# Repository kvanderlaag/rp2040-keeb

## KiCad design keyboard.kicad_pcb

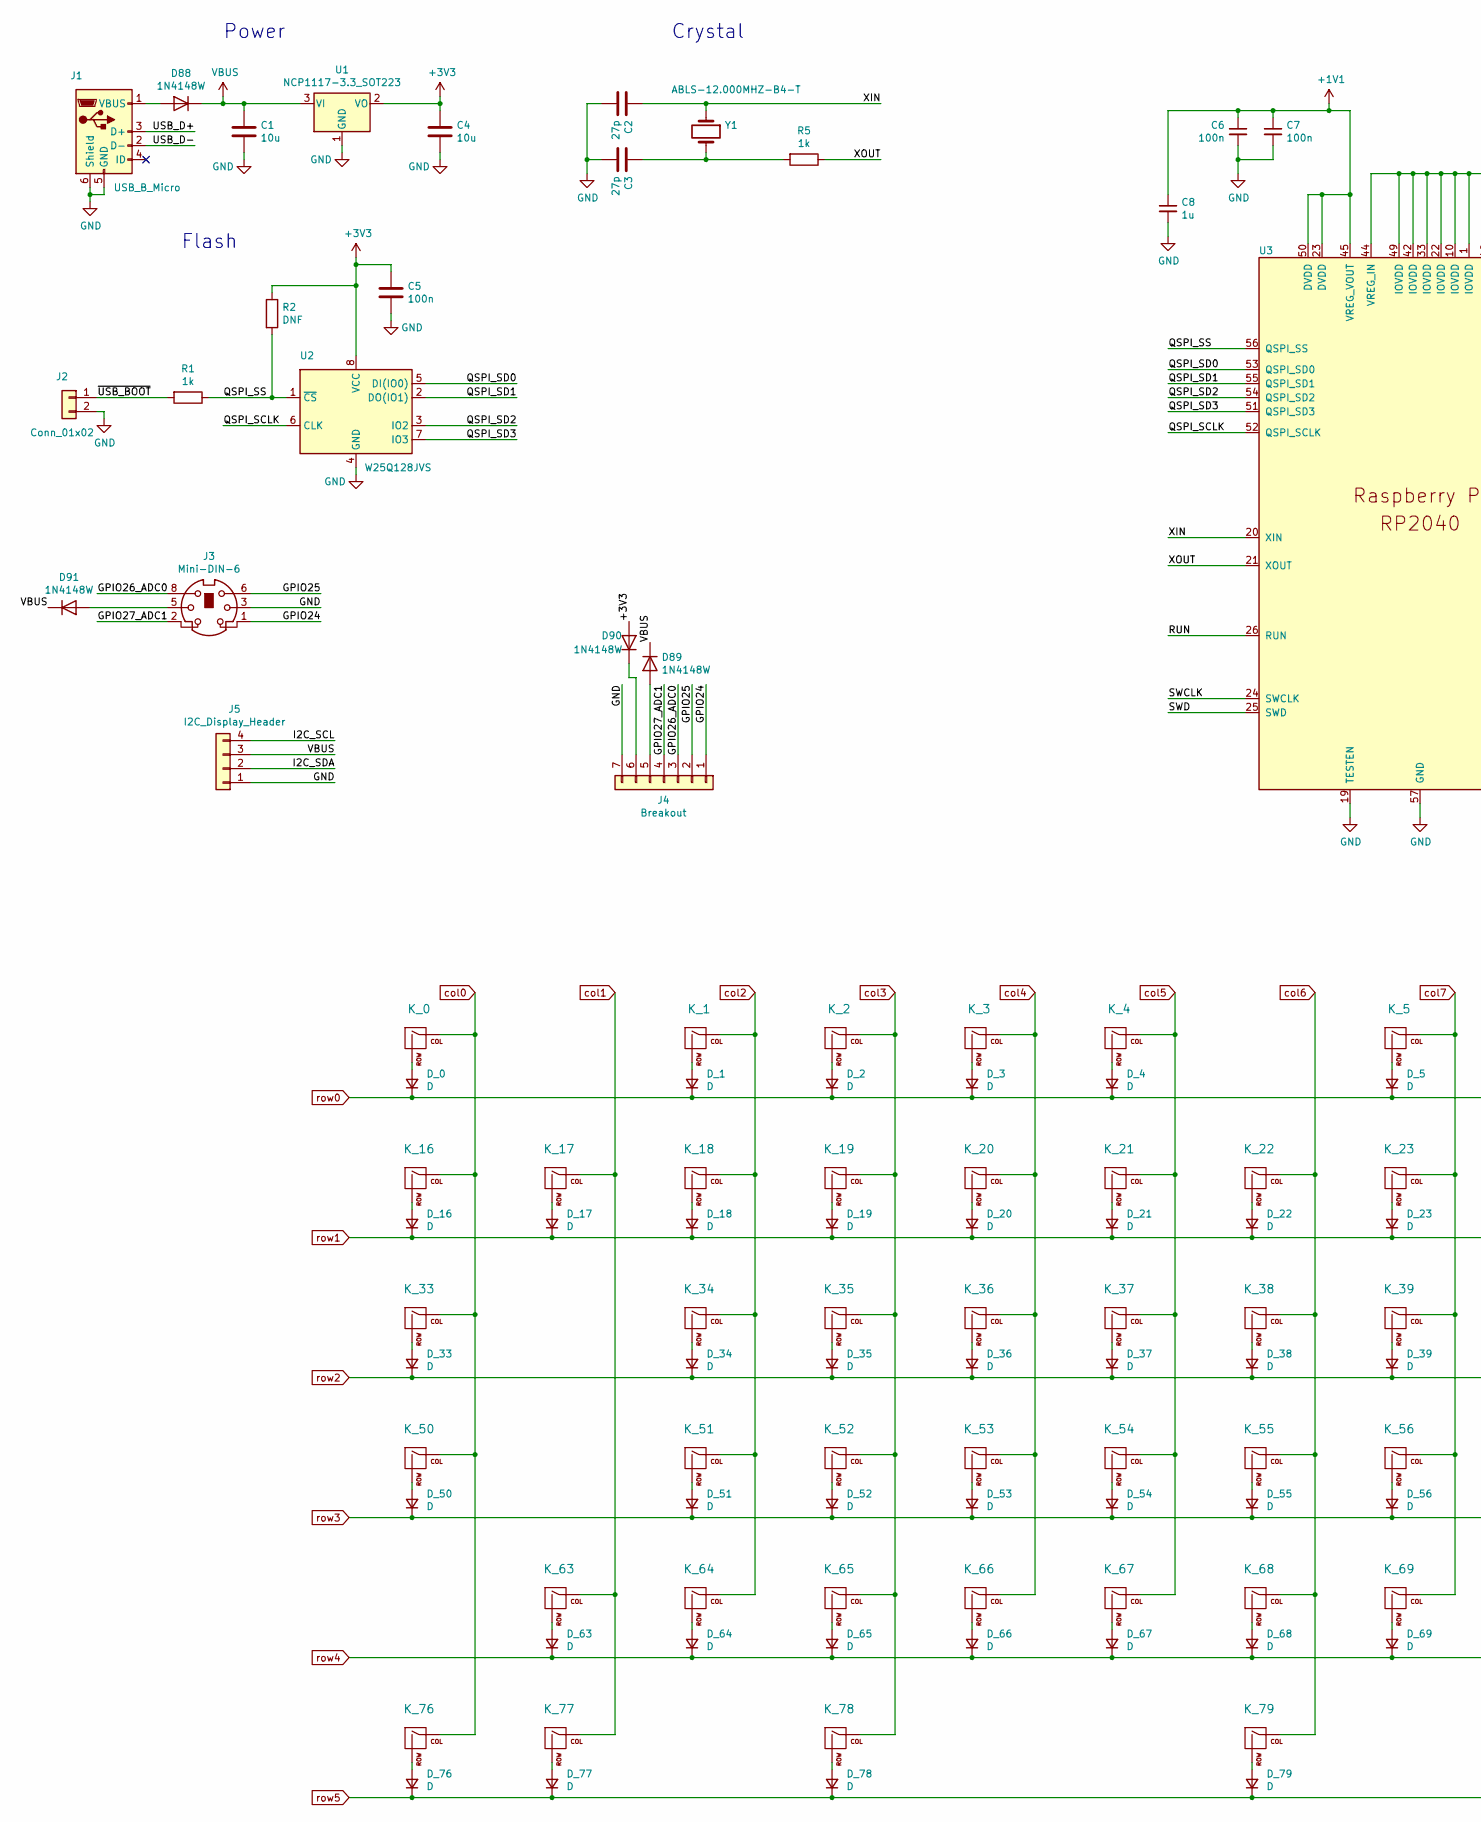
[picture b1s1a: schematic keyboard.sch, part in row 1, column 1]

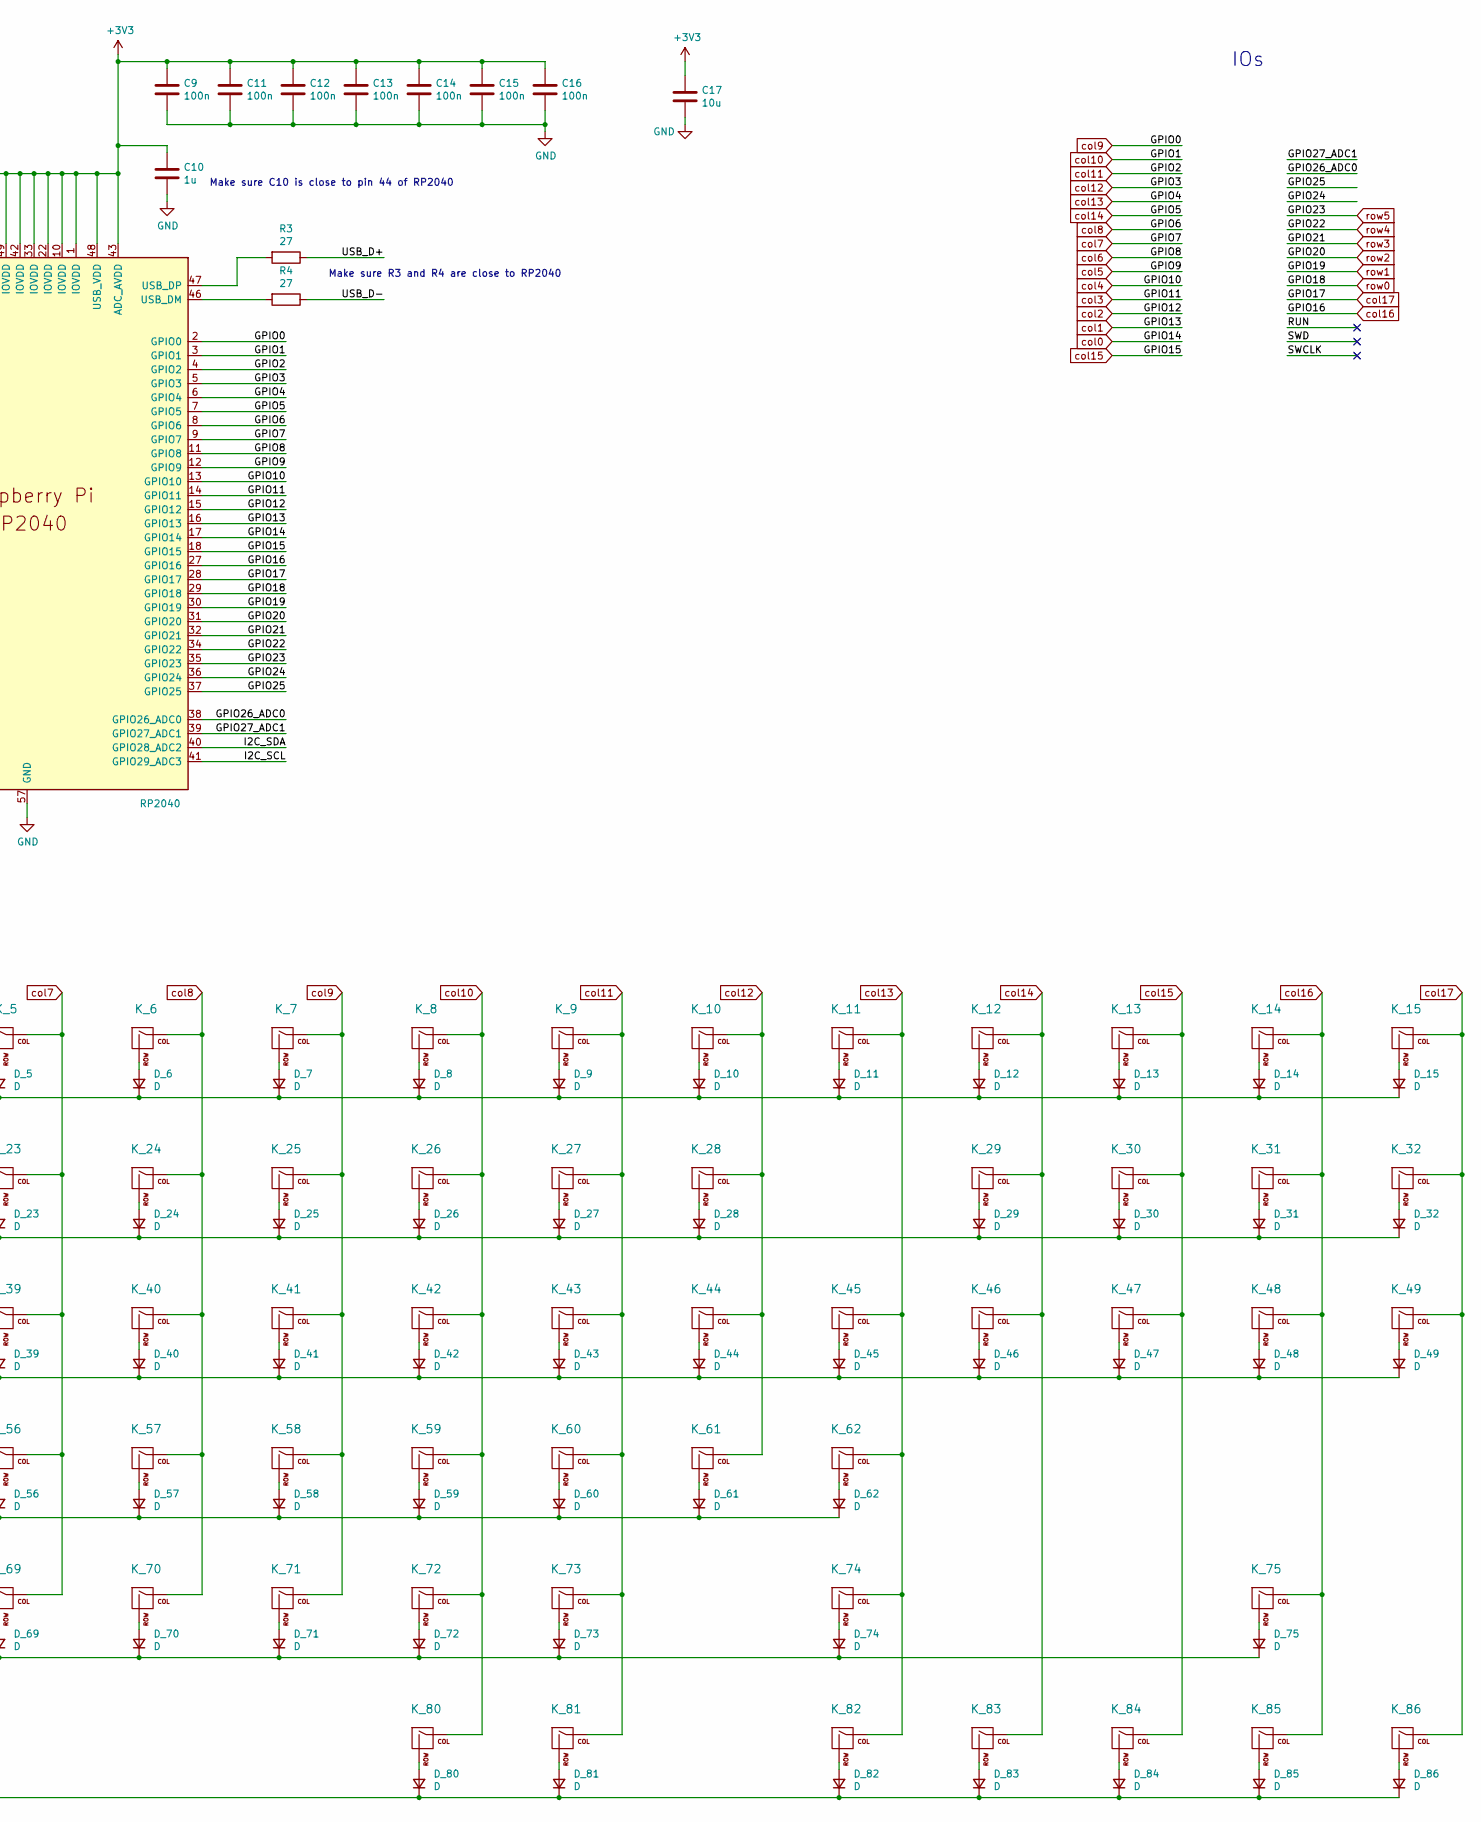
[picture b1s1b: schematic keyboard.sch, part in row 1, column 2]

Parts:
C1, C4, C17: 10u; C_0805_2012Metric
C2, C3: 27p; C_0402_1005Metric
C5, C6, C7, C9, C11, C12, C13, C14, C15, C16: 100n; C_0402_1005Metric
C8, C10: 1u; C_0402_1005Metric
D88, D89, D90, D91: 1N4148W; D_0402_1005Metric
D_0, D_1, D_2, D_3, D_4, D_5, D_6, D_7, D_8, D_9, D_10, D_11, D_12, D_13, D_14, D_15, D_16, D_17, D_18, D_19, D_20, D_21, D_22, D_23, D_24, D_25, D_26, D_27, D_28, D_29, D_30, D_31, D_32, D_33, D_34, D_35, D_36, D_37, D_38, D_39, D_40, D_41, D_42, D_43, D_44, D_45, D_46, D_47, D_48, D_49, D_50, D_51, D_52, D_53, D_54, D_55, D_56, D_57, D_58, D_59, D_60, D_61, D_62, D_63, D_64, D_65, D_66, D_67, D_68, D_69, D_70, D_71, D_72, D_73, D_74, D_75, D_76, D_77, D_78, D_79, D_80, D_81, D_82, D_83, D_84, D_85, D_86: D; D_SOD-123
J1: USB_B_Micro; USB_Micro-B_Amphenol_10103594-0001LF_Horizontal_modified
J2: Conn_01x02; PinHeader_1x02_P2.54mm_Vertical
J3: Mini-DIN-6; MJD-006-FS
J4: Breakout; PinHeader_1x07_P2.54mm_Vertical
J5: I2C_Display_Header; PinHeader_1x04_P2.54mm_Horizontal
K_0, K_1, K_2, K_3, K_4, K_5, K_6, K_7, K_8, K_9, K_10, K_11, K_12, K_13, K_14, K_15, K_16, K_17, K_18, K_19, K_20, K_21, K_22, K_23, K_24, K_25, K_26, K_27, K_28, K_30, K_31, K_32, K_34, K_35, K_36, K_37, K_38, K_39, K_40, K_41, K_42, K_43, K_44, K_45, K_47, K_48, K_49, K_51, K_52, K_53, K_54, K_55, K_56, K_57, K_58, K_59, K_60, K_61, K_64, K_65, K_66, K_67, K_68, K_69, K_70, K_71, K_72, K_73, K_75, K_84, K_85, K_86: KEYSW; MX-1U-NoLED
K_29: KEYSW; MX-2U-NoLED
K_33, K_46: KEYSW; MX-1.5U-NoLED
K_50: KEYSW; MX-1.75U-NoLED
K_62, K_63: KEYSW; MX-2.25U-NoLED
K_74: KEYSW; MX-2.75U-NoLED
K_76, K_77, K_78, K_80, K_81, K_82, K_83: KEYSW; MX-1.25U-NoLED
K_79: KEYSW; MX-6.25U-NoLED
R1, R5: 1k; C_0402_1005Metric
R2: DNF; C_0402_1005Metric
R3, R4: 27; C_0402_1005Metric
U1: NCP1117-3.3_SOT223; SOT-223-3_TabPin2
U2: W25Q128JVS; SOIC-8_5.23x5.23mm_P1.27mm
U3: RP2040; RP2040-QFN-56
Y1: ABLS-12.000MHZ-B4-T; Crystal_SMD_HC49-US

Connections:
+1V1: C6.1, C7.1, C8.1, U3.23 (DVDD), U3.45 (VREG_VOUT), U3.50 (DVDD)
+3V3: C4.1, C5.1, C9.1, C10.1, C11.1, C12.1, C13.1, C14.1, C15.1, C16.1, C17.1, D90.2 (A), R2.1, U1.2 (VO), U2.8 (VCC), U3.1 (IOVDD), U3.10 (IOVDD), U3.22 (IOVDD), U3.33 (IOVDD), U3.42 (IOVDD), U3.43 (ADC_AVDD), U3.44 (VREG_IN), U3.48 (USB_VDD), U3.49 (IOVDD)
/GPIO24: J3.1, J4.1, U3.36 (GPIO24)
/GPIO25: J3.6, J4.2, U3.37 (GPIO25)
/GPIO26_ADC0: J3.8, J4.3, U3.38 (GPIO26_ADC0)
/GPIO27_ADC1: J3.2, J4.4, U3.39 (GPIO27_ADC1)
/I2C_SCL: J5.4, U3.41 (GPIO29_ADC3)
/I2C_SDA: J5.2, U3.40 (GPIO28_ADC2)
/QSPI_SCLK: U2.6 (CLK), U3.52 (QSPI_SCLK)
/QSPI_SD0: U2.5 (DI(IO0)), U3.53 (QSPI_SD0)
/QSPI_SD1: U2.2 (DO(IO1)), U3.55 (QSPI_SD1)
/QSPI_SD2: U2.3 (IO2), U3.54 (QSPI_SD2)
/QSPI_SD3: U2.7 (IO3), U3.51 (QSPI_SD3)
/QSPI_SS: R1.1, R2.2, U2.1 (~CS), U3.56 (QSPI_SS)
/RUN: U3.26 (RUN)
/SWCLK: U3.24 (SWCLK)
/SWD: U3.25 (SWD)
/USB_D+: J1.3 (D+), R3.1
/USB_D-: J1.2 (D-), R4.1
/XIN: C2.1, U3.20 (XIN), Y1.1
/XOUT: R5.1, U3.21 (XOUT)
/~USB_BOOT: J2.1, R1.2
GND: C1.2, C2.2, C3.2, C4.2, C5.2, C6.2, C7.2, C8.2, C9.2, C10.2, C11.2, C12.2, C13.2, C14.2, C15.2, C16.2, C17.2, J1.5 (GND), J1.6 (Shield), J2.2, J3.3, J4.7, J5.1, U1.1 (GND), U2.4 (GND), U3.19 (TESTEN), U3.57 (GND)
unnamed: C3.1, R5.2, Y1.2
unnamed: D88.2 (A), J1.1 (VBUS)
unnamed: D89.2 (A), J4.5
unnamed: D90.1 (K), J4.6
unnamed: D91.2 (A), J3.5
unnamed: D_0.2 (A), K_0.2 (ROW)
unnamed: D_1.2 (A), K_1.2 (ROW)
unnamed: D_2.2 (A), K_2.2 (ROW)
unnamed: D_3.2 (A), K_3.2 (ROW)
unnamed: D_4.2 (A), K_4.2 (ROW)
unnamed: D_5.2 (A), K_5.2 (ROW)
unnamed: D_6.2 (A), K_6.2 (ROW)
unnamed: D_7.2 (A), K_7.2 (ROW)
unnamed: D_8.2 (A), K_8.2 (ROW)
unnamed: D_9.2 (A), K_9.2 (ROW)
unnamed: D_10.2 (A), K_10.2 (ROW)
unnamed: D_11.2 (A), K_11.2 (ROW)
unnamed: D_12.2 (A), K_12.2 (ROW)
unnamed: D_13.2 (A), K_13.2 (ROW)
unnamed: D_14.2 (A), K_14.2 (ROW)
unnamed: D_15.2 (A), K_15.2 (ROW)
unnamed: D_16.2 (A), K_16.2 (ROW)
unnamed: D_17.2 (A), K_17.2 (ROW)
unnamed: D_18.2 (A), K_18.2 (ROW)
unnamed: D_19.2 (A), K_19.2 (ROW)
unnamed: D_20.2 (A), K_20.2 (ROW)
unnamed: D_21.2 (A), K_21.2 (ROW)
unnamed: D_22.2 (A), K_22.2 (ROW)
unnamed: D_23.2 (A), K_23.2 (ROW)
unnamed: D_24.2 (A), K_24.2 (ROW)
unnamed: D_25.2 (A), K_25.2 (ROW)
unnamed: D_26.2 (A), K_26.2 (ROW)
unnamed: D_27.2 (A), K_27.2 (ROW)
unnamed: D_28.2 (A), K_28.2 (ROW)
unnamed: D_29.2 (A), K_29.2 (ROW)
unnamed: D_30.2 (A), K_30.2 (ROW)
unnamed: D_31.2 (A), K_31.2 (ROW)
unnamed: D_32.2 (A), K_32.2 (ROW)
unnamed: D_33.2 (A), K_33.2 (ROW)
unnamed: D_34.2 (A), K_34.2 (ROW)
unnamed: D_35.2 (A), K_35.2 (ROW)
unnamed: D_36.2 (A), K_36.2 (ROW)
unnamed: D_37.2 (A), K_37.2 (ROW)
unnamed: D_38.2 (A), K_38.2 (ROW)
unnamed: D_39.2 (A), K_39.2 (ROW)
unnamed: D_40.2 (A), K_40.2 (ROW)
unnamed: D_41.2 (A), K_41.2 (ROW)
unnamed: D_42.2 (A), K_42.2 (ROW)
unnamed: D_43.2 (A), K_43.2 (ROW)
unnamed: D_44.2 (A), K_44.2 (ROW)
unnamed: D_45.2 (A), K_45.2 (ROW)
unnamed: D_46.2 (A), K_46.2 (ROW)
unnamed: D_47.2 (A), K_47.2 (ROW)
unnamed: D_48.2 (A), K_48.2 (ROW)
unnamed: D_49.2 (A), K_49.2 (ROW)
unnamed: D_50.2 (A), K_50.2 (ROW)
unnamed: D_51.2 (A), K_51.2 (ROW)
unnamed: D_52.2 (A), K_52.2 (ROW)
unnamed: D_53.2 (A), K_53.2 (ROW)
unnamed: D_54.2 (A), K_54.2 (ROW)
unnamed: D_55.2 (A), K_55.2 (ROW)
unnamed: D_56.2 (A), K_56.2 (ROW)
unnamed: D_57.2 (A), K_57.2 (ROW)
unnamed: D_58.2 (A), K_58.2 (ROW)
unnamed: D_59.2 (A), K_59.2 (ROW)
unnamed: D_60.2 (A), K_60.2 (ROW)
unnamed: D_61.2 (A), K_61.2 (ROW)
unnamed: D_62.2 (A), K_62.2 (ROW)
unnamed: D_63.2 (A), K_63.2 (ROW)
unnamed: D_64.2 (A), K_64.2 (ROW)
unnamed: D_65.2 (A), K_65.2 (ROW)
unnamed: D_66.2 (A), K_66.2 (ROW)
unnamed: D_67.2 (A), K_67.2 (ROW)
unnamed: D_68.2 (A), K_68.2 (ROW)
unnamed: D_69.2 (A), K_69.2 (ROW)
unnamed: D_70.2 (A), K_70.2 (ROW)
unnamed: D_71.2 (A), K_71.2 (ROW)
unnamed: D_72.2 (A), K_72.2 (ROW)
unnamed: D_73.2 (A), K_73.2 (ROW)
unnamed: D_74.2 (A), K_74.2 (ROW)
unnamed: D_75.2 (A), K_75.2 (ROW)
unnamed: D_76.2 (A), K_76.2 (ROW)
unnamed: D_77.2 (A), K_77.2 (ROW)
unnamed: D_78.2 (A), K_78.2 (ROW)
unnamed: D_79.2 (A), K_79.2 (ROW)
unnamed: D_80.2 (A), K_80.2 (ROW)
unnamed: D_81.2 (A), K_81.2 (ROW)
unnamed: D_82.2 (A), K_82.2 (ROW)
unnamed: D_83.2 (A), K_83.2 (ROW)
unnamed: D_84.2 (A), K_84.2 (ROW)
unnamed: D_85.2 (A), K_85.2 (ROW)
unnamed: D_86.2 (A), K_86.2 (ROW)
unnamed: R3.2, U3.47 (USB_DP)
unnamed: R4.2, U3.46 (USB_DM)
VBUS: C1.1, D88.1 (K), D89.1 (K), D91.1 (K), J5.3, U1.3 (VI)
col0: K_0.1 (COL), K_16.1 (COL), K_33.1 (COL), K_50.1 (COL), K_76.1 (COL), U3.17 (GPIO14)
col1: K_17.1 (COL), K_63.1 (COL), K_77.1 (COL), U3.16 (GPIO13)
col2: K_1.1 (COL), K_18.1 (COL), K_34.1 (COL), K_51.1 (COL), K_64.1 (COL), U3.15 (GPIO12)
col3: K_2.1 (COL), K_19.1 (COL), K_35.1 (COL), K_52.1 (COL), K_65.1 (COL), K_78.1 (COL), U3.14 (GPIO11)
col4: K_3.1 (COL), K_20.1 (COL), K_36.1 (COL), K_53.1 (COL), K_66.1 (COL), U3.13 (GPIO10)
col5: K_4.1 (COL), K_21.1 (COL), K_37.1 (COL), K_54.1 (COL), K_67.1 (COL), U3.12 (GPIO9)
col6: K_22.1 (COL), K_38.1 (COL), K_55.1 (COL), K_68.1 (COL), K_79.1 (COL), U3.11 (GPIO8)
col7: K_5.1 (COL), K_23.1 (COL), K_39.1 (COL), K_56.1 (COL), K_69.1 (COL), U3.9 (GPIO7)
col8: K_6.1 (COL), K_24.1 (COL), K_40.1 (COL), K_57.1 (COL), K_70.1 (COL), U3.8 (GPIO6)
col9: K_7.1 (COL), K_25.1 (COL), K_41.1 (COL), K_58.1 (COL), K_71.1 (COL), U3.2 (GPIO0)
col10: K_8.1 (COL), K_26.1 (COL), K_42.1 (COL), K_59.1 (COL), K_72.1 (COL), K_80.1 (COL), U3.3 (GPIO1)
col11: K_9.1 (COL), K_27.1 (COL), K_43.1 (COL), K_60.1 (COL), K_73.1 (COL), K_81.1 (COL), U3.4 (GPIO2)
col12: K_10.1 (COL), K_28.1 (COL), K_44.1 (COL), K_61.1 (COL), U3.5 (GPIO3)
col13: K_11.1 (COL), K_45.1 (COL), K_62.1 (COL), K_74.1 (COL), K_82.1 (COL), U3.6 (GPIO4)
col14: K_12.1 (COL), K_29.1 (COL), K_46.1 (COL), K_83.1 (COL), U3.7 (GPIO5)
col15: K_13.1 (COL), K_30.1 (COL), K_47.1 (COL), K_84.1 (COL), U3.18 (GPIO15)
col16: K_14.1 (COL), K_31.1 (COL), K_48.1 (COL), K_75.1 (COL), K_85.1 (COL), U3.27 (GPIO16)
col17: K_15.1 (COL), K_32.1 (COL), K_49.1 (COL), K_86.1 (COL), U3.28 (GPIO17)
row0: D_0.1 (K), D_1.1 (K), D_2.1 (K), D_3.1 (K), D_4.1 (K), D_5.1 (K), D_6.1 (K), D_7.1 (K), D_8.1 (K), D_9.1 (K), D_10.1 (K), D_11.1 (K), D_12.1 (K), D_13.1 (K), D_14.1 (K), D_15.1 (K), U3.29 (GPIO18)
row1: D_16.1 (K), D_17.1 (K), D_18.1 (K), D_19.1 (K), D_20.1 (K), D_21.1 (K), D_22.1 (K), D_23.1 (K), D_24.1 (K), D_25.1 (K), D_26.1 (K), D_27.1 (K), D_28.1 (K), D_29.1 (K), D_30.1 (K), D_31.1 (K), D_32.1 (K), U3.30 (GPIO19)
row2: D_33.1 (K), D_34.1 (K), D_35.1 (K), D_36.1 (K), D_37.1 (K), D_38.1 (K), D_39.1 (K), D_40.1 (K), D_41.1 (K), D_42.1 (K), D_43.1 (K), D_44.1 (K), D_45.1 (K), D_46.1 (K), D_47.1 (K), D_48.1 (K), D_49.1 (K), U3.31 (GPIO20)
row3: D_50.1 (K), D_51.1 (K), D_52.1 (K), D_53.1 (K), D_54.1 (K), D_55.1 (K), D_56.1 (K), D_57.1 (K), D_58.1 (K), D_59.1 (K), D_60.1 (K), D_61.1 (K), D_62.1 (K), U3.32 (GPIO21)
row4: D_63.1 (K), D_64.1 (K), D_65.1 (K), D_66.1 (K), D_67.1 (K), D_68.1 (K), D_69.1 (K), D_70.1 (K), D_71.1 (K), D_72.1 (K), D_73.1 (K), D_74.1 (K), D_75.1 (K), U3.34 (GPIO22)
row5: D_76.1 (K), D_77.1 (K), D_78.1 (K), D_79.1 (K), D_80.1 (K), D_81.1 (K), D_82.1 (K), D_83.1 (K), D_84.1 (K), D_85.1 (K), D_86.1 (K), U3.35 (GPIO23)

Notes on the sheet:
Make sure C10 is close to pin 44 of RP2040
Crystal
Flash
Power
IOs
Make sure R3 and R4 are close to RP2040

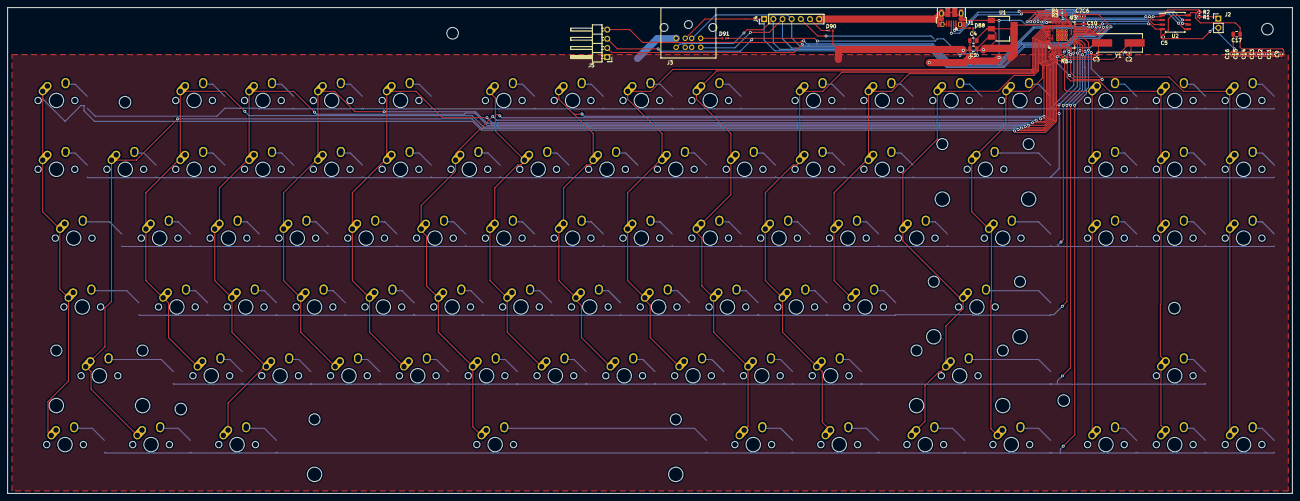
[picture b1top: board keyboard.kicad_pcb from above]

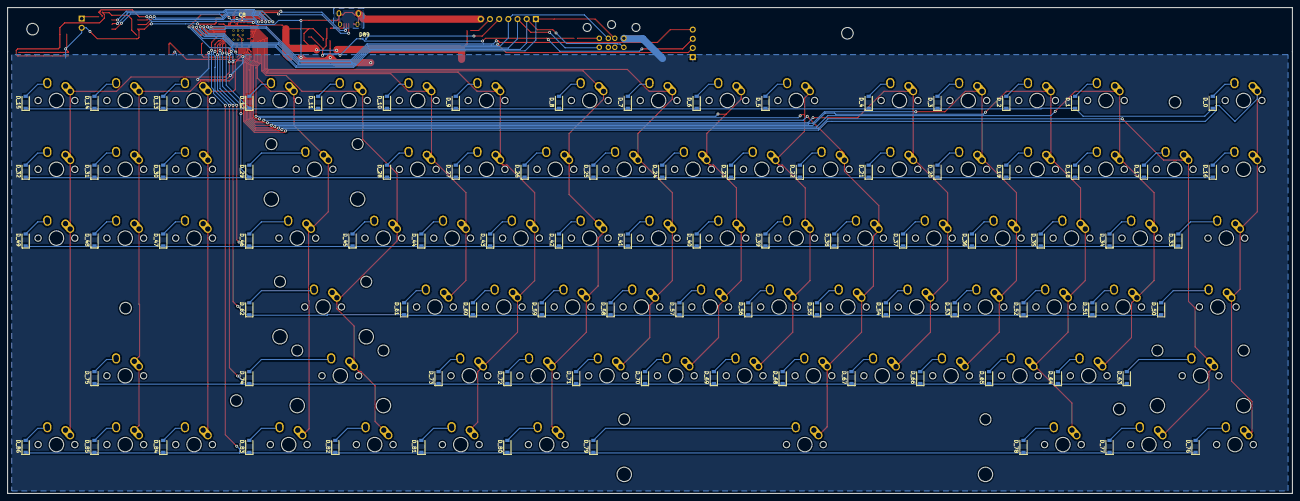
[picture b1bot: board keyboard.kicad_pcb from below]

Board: 2 copper layers, 355.7 x 134.5 mm, 209 parts (89 on the bottom side), 139 nets.

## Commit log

2023-01-21 add breakout, mini-DIN, and display headers; re-route
